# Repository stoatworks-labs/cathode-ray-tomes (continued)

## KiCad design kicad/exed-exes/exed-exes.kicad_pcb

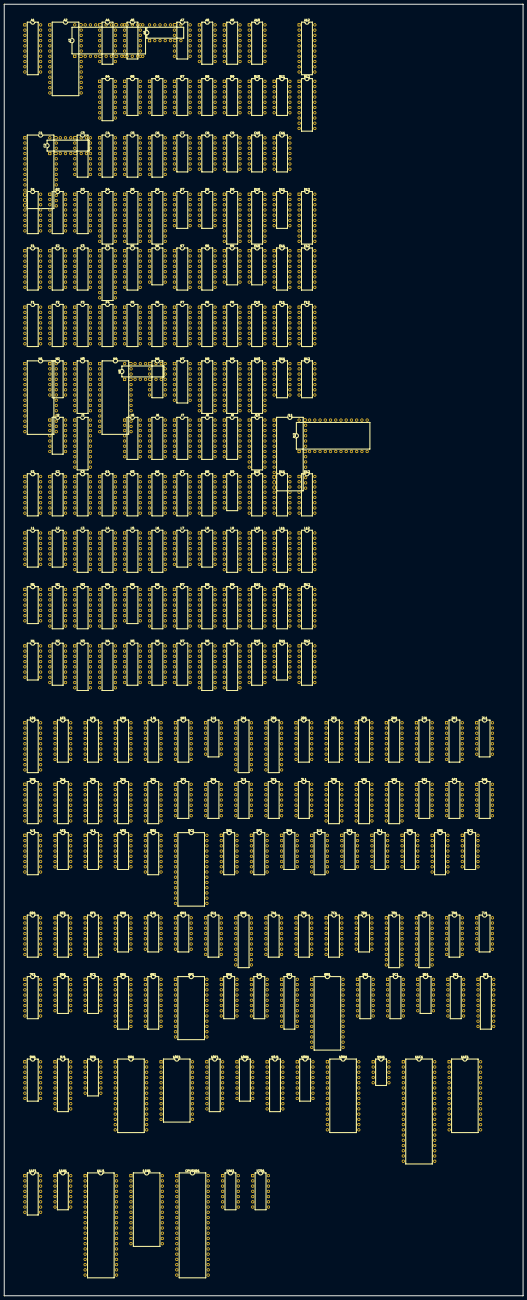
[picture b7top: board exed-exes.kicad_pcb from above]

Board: 2 copper layers, 251.8 x 626.8 mm, 235 parts (0 on the bottom side), 913 nets, no tracks yet.

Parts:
1D1, 7E1, 8D1, 8E1: 74LS273; DIP-20_W7.62mm
1E1, 2E1: 74LS153; DIP-16_W7.62mm
1F1, 1H1, 2F1, 2H1, 6E1, 7A1, 7C1, 7K1: 74LS174; DIP-16_W7.62mm
1J1, 1K1, 2J1, 2K1: 74LS161; DIP-16_W7.62mm
1L1, 5L1, 7D1: 74LS04; DIP-14_W7.62mm
2A1, 2B1, 7F1, 8K1, 9J1, 10F1, 10J1: 74LS245; DIP-20_W7.62mm
2D1, 3D1, 4D1, 6F1, 6L1: TBP24S10N; DIP-16_W7.62mm
2L1, 3J1, 3L1, 4H1, 4L1, 4M1, 6K1, 7J1: 74LS74; DIP-14_W7.62mm
2M1, 3A1, 4J1, 7B1, 9B1, 9E1, 10K1: 74LS138; DIP-16_W7.62mm
3B1: 74LS139; DIP-16_W7.62mm
3E1: TBP18S030; DIP-16_W7.62mm
3F1, 3H1: 74LS20; DIP-14_W7.62mm
3K1: 74LS30; DIP-14_W7.62mm
3M1: 74LS112; DIP-16_W7.62mm
4B1, 5B1, 5J1, 6B1, 8J1, 9C1: 74LS367; DIP-16_W7.62mm
4E1, 6H1: 74LS32; DIP-14_W7.62mm
4F1, 4K1, 5M1, 9D1, 9K1: 74LS08; DIP-14_W7.62mm
5C1: 2764; DIP-28_W15.24mm
5E1, 6D1: 74LS194; DIP-16_W7.62mm
5F1, 7H1, 8H1, 9H1: 74LS157; DIP-16_W7.62mm
5H1, 6J1: 74LS00; DIP-14_W7.62mm
5K1: 74LS10; DIP-14_W7.62mm
6C1: 74LS86; DIP-14_W7.62mm
6M1, 9F1: 74LS374; DIP-20_W7.62mm
8B1, 8C1: 74HC74; DIP-14_W7.62mm
8F1, 10E1: MSM2128-20RS; DIP-24_W15.24mm
8M1: TC5565; DIP-28_W15.24mm
9M1, 10M1, 11E1, 11M1: 27128; DIP-28_W15.24mm
10H1, 11F1: SN76489AN; DIP-16_W7.62mm
11A1: HA1368-R; DIP-10_W7.62mm
11C1: AY-3-8910; DIP-40_W15.24mm
11H1: 74LS14; DIP-14_W7.62mm
11J1: Z80CPU; DIP-40_W15.24mm
A1: 74LS273; DIP-20_W7.62mm
A2, A3: 27128; DIP-28_W15.24mm
A4: 74LS194; DIP-16_W7.62mm
A5, A6: 74LS74; DIP-14_W7.62mm
A7: 74LS32; DIP-14_W7.62mm
A8, A9, A10: 74LS161; DIP-16_W7.62mm
A12: 74LS245; DIP-20_W7.62mm
B4: 74LS194; DIP-16_W7.62mm
B5, B9: 74LS10; DIP-14_W7.62mm
B6: 74LS04; DIP-14_W7.62mm
B7: 74LS08; DIP-14_W7.62mm
B8: 74LS00; DIP-14_W7.62mm
B10, B11: MN2114; DIP-14_W7.62mm
B12: 74LS245; DIP-20_W7.62mm
C1: 27128; DIP-28_W15.24mm
C2, C3: 74LS194; DIP-16_W7.62mm
C4: TBP24S10N; DIP-16_W7.62mm
C5, C6: 74LS174; DIP-16_W7.62mm
C7, C10: 74LS32; DIP-14_W7.62mm
C8: 74LS08; DIP-14_W7.62mm
C9: 74LS04; DIP-14_W7.62mm
C11: 74LS74; DIP-14_W7.62mm
CPUSND1: Z80CPU; DIP-40_W15.24mm
D1, D2, D3: 74LS283; DIP-16_W7.62mm
D4, D5, D6: 74LS273; DIP-20_W7.62mm
D7, D8: MN2114; DIP-14_W7.62mm
D9, D10, D12: 74LS245; DIP-20_W7.62mm
D11: 74LS20; DIP-14_W7.62mm
E1, E2, E3, E11, E12: 74LS283; DIP-16_W7.62mm
E4: 74LS273; DIP-20_W7.62mm
E5: 74LS138; DIP-16_W7.62mm
E6: 74LS86; DIP-14_W7.62mm
E7, E8: 74LS157; DIP-16_W7.62mm
E9, E10: MN2114; DIP-14_W7.62mm
F1, F2: 74LS174; DIP-16_W7.62mm
F3, F4, F11, F12: 74LS283; DIP-16_W7.62mm
F5, F6: 74LS161; DIP-16_W7.62mm
F7, F8, F9, F10: 74LS157; DIP-16_W7.62mm
H1: 27128; DIP-28_W15.24mm
H2: 74LS86; DIP-14_W7.62mm
H3, H9, H10: 74LS273; DIP-20_W7.62mm
H4: 2764; DIP-28_W15.24mm
H5, H7: 74LS283; DIP-16_W7.62mm
H6: 74LS20; DIP-14_W7.62mm
H8: 74LS373; DIP-20_W7.62mm
H11, H12: 74LS04; DIP-14_W7.62mm
J2: 74LS86; DIP-14_W7.62mm
J3, J10: 74LS273; DIP-20_W7.62mm
J5, J7, J8: 74LS283; DIP-16_W7.62mm
J6: 74LS175; DIP-16_W7.62mm
J9: 74LS174; DIP-16_W7.62mm
J11, J12: 27128; DIP-28_W15.24mm
K1, K2, K10, K11, K12: 74LS194; DIP-16_W7.62mm
K3: 74LS157; DIP-16_W7.62mm
K4, K5: 74LS174; DIP-16_W7.62mm
K6: TBP24S10N; DIP-16_W7.62mm
K7: 74LS175; DIP-16_W7.62mm
K8: 74LS283; DIP-16_W7.62mm
K9: 74LS86; DIP-14_W7.62mm
L1: 74LS10; DIP-14_W7.62mm
L2, L7: 74LS04; DIP-14_W7.62mm
L3, L4, L9, L10: TBP24S10N; DIP-16_W7.62mm
L5, L6: 74LS139; DIP-16_W7.62mm
L8: 74LS32; DIP-14_W7.62mm
L11: 74LS157; DIP-16_W7.62mm
L12: 74LS194; DIP-16_W7.62mm
M1: 74LS74; DIP-14_W7.62mm
M2, M11: 74LS174; DIP-16_W7.62mm
M3, M4, M9, M10: 74LS257; DIP-16_W7.62mm
M5: 74LS00; DIP-14_W7.62mm
M6, M7, M8: 74LS163; DIP-16_W7.62mm
M12: 74LS157; DIP-16_W7.62mm
N1: 74LS74; DIP-14_W7.62mm
N2, N10: 74LS174; DIP-16_W7.62mm
N3, N4, N8, N9: HM6148; DIP-18_W7.62mm
N5, N6, N7: 74LS163; DIP-16_W7.62mm
N11: 74LS20; DIP-14_W7.62mm
N12: 74LS157; DIP-16_W7.62mm
U4K1: 74LS08; DIP-14_W7.62mm
U7D1: 74LS04; DIP-14_W7.62mm

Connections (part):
/main/ram_rom/ROM~CE1: 9K1.8, 9M1.20
/main/ram_rom/ROM~CE2: 9K1.6, 10M1.20
/main/ram_rom/ROM~CE3: 9K1.3, 11M1.20
/main/ram_rom/~CS01: 9K1.1, 10K1.15
/main/ram_rom/~CS23: 9K1.2, 10K1.14
/main/ram_rom/~CS45: 9K1.5, 10K1.13
/main/ram_rom/~CS67: 9K1.4, 10K1.12
/main/ram_rom/~CS89: 9K1.10, 10K1.11
/main/ram_rom/~CSAB: 9K1.9, 10K1.10
/main/ram_rom/~CSEF: 9K1.12, 10K1.7
/main/~WAIT: 6J1.8, 11J1.24
/sound/SA0: 9E1.1, 10E1.8, 11E1.10, CPUSND1.30
/sound/SA1: 9E1.2, 10E1.7, 11E1.9, CPUSND1.31
/sound/SA2: 9E1.3, 10E1.6, 11E1.8, CPUSND1.32
/sound/SA3: 10E1.5, 11E1.7, CPUSND1.33
/sound/SA4: 10E1.4, 11E1.6, CPUSND1.34
/sound/SA5: 10E1.3, 11E1.5, CPUSND1.35
/sound/SA6: 10E1.2, 11E1.4, CPUSND1.36
/sound/SA7: 10E1.1, 11E1.3, CPUSND1.37
/sound/SA8: 10E1.23, 11E1.25, CPUSND1.38
/sound/SA9: 10E1.22, 11E1.24, CPUSND1.39
/sound/SA10: 10E1.19, 11E1.21, CPUSND1.40
/sound/SA11: 11E1.23, CPUSND1.1
/sound/SA12: 11E1.2, CPUSND1.2
/sound/SA13: 9B1.1, 11E1.26, CPUSND1.3
/sound/SA14: 9B1.2, CPUSND1.4
/sound/SA15: 9B1.3, CPUSND1.5
/sound/snd_c_latch/SDB0: 10F1.11, 10H1.3, 11F1.3
/sound/snd_c_latch/SDB1: 10F1.12, 10H1.2, 11F1.2
/sound/snd_c_latch/SDB2: 10F1.13, 10H1.1, 11F1.1
/sound/snd_c_latch/SDB3: 10F1.14, 10H1.15, 11F1.15
/sound/snd_c_latch/SDB4: 10F1.15, 10H1.13, 11F1.13
/sound/snd_c_latch/SDB5: 10F1.16, 10H1.12, 11F1.12
/sound/snd_c_latch/SDB6: 10F1.17, 10H1.11, 11F1.11
/sound/snd_c_latch/SDB7: 10F1.18, 10H1.10, 11F1.10
/sound/snd_c_latch/SG_CLK: 8B1.3, 8B1.11, 8C1.11, 9C1.12, 9C1.13, 10H1.14, 11F1.14
/sound/snd_c_latch/VCC: 7B1.6, 8B1.1, 8B1.4, 8B1.10, 8B1.13, 8C1.10, 8C1.13, C11.1, E5.6
/sound/snd_c_latch/VSS: 9C1.1, 9C1.15, 10F1.1, C11.2
/sound/~SIORQ: 8C1.4, CPUSND1.20
/sound/~SMREQ: 9B1.4, CPUSND1.19
/sound/~SRAMCS: 9B1.13, 10E1.18
/sound/~SRFSH: 9B1.6, CPUSND1.28
/sound/~SROMCE: 9D1.11, 11E1.20
/video/char/0: 8D1.8, 8E1.2
/video/char/1: 8D1.7, 8E1.5
/video/char/2: 8D1.4, 8E1.6
/video/char/3: 8D1.3, 8E1.9
/video/char/4: 8D1.18, 8E1.12
/video/char/5: 8D1.17, 8E1.15
/video/char/6: 8D1.14, 8E1.16
/video/char/7: 8D1.13, 8E1.19
/video/char/AC0: 5C1.6, 8D1.9
/video/char/AC1: 5C1.5, 8D1.6
/video/char/AC2: 5C1.4, 8D1.5
/video/char/AC3: 5C1.3, 8D1.2
/video/char/AC4: 5C1.25, 8D1.19
/video/char/AC5: 5C1.24, 8D1.16
/video/char/AC6: 5C1.21, 8D1.15
/video/char/AC7: 5C1.23, 8D1.12
/video/char/AC8: 5C1.2, 7E1.19
/video/char/CC0: 6E1.15, 6F1.7
/video/char/CC1: 6E1.2, 6F1.4
/video/char/CC2: 6E1.5, 6F1.3
/video/char/CC3: 6E1.7, 6F1.2
/video/char/CC4: 6E1.10, 6F1.1
/video/char/CC5: 5F1.1, 6E1.12, 6F1.15
/video/char/CHAROM_A0: 6C1.9, 7C1.5
/video/char/CHAROM_A1: 6C1.13, 7C1.15
/video/char/CHAROM_A2: 6C1.4, 7C1.12
/video/char/CR_Q0: 5E1.15, 5F1.2
/video/char/CR_QQ0: 5F1.5, 6D1.15
/video/char/CR_QQ3: 5F1.6, 6D1.12
/video/char/DD0: 6E1.14, 7E1.2
/video/char/DD1: 6E1.3, 7E1.5
/video/char/DD2: 6E1.4, 7E1.6
/video/char/DD3: 6E1.6, 7E1.9
/video/char/DD4: 6E1.11, 7E1.12
/video/char/DD5: 6E1.13, 7D1.13, 7E1.15
/video/char/S0: 5E1.9, 5F1.9, 6D1.9
/video/char/S1: 5E1.10, 5F1.12, 6D1.10
/video/char/VFLIP: 6C1.5, 6C1.10, 6C1.12, 7E1.16
/video/colmix/CEX0: 1D1.17, 4E1.6
/video/colmix/CEX1: 1D1.8, 4E1.8
/video/colmix/CMUX0: 1D1.14, 2E1.7
/video/colmix/CMUX1: 1D1.7, 2E1.9
/video/colmix/CMUX2: 1D1.13, 1E1.9
/video/colmix/CMUX3: 1D1.4, 1E1.7
/video/colmix/COLA0: 1D1.15, 2D1.5, 3D1.5, 4D1.5
/video/colmix/COLA1: 1D1.6, 2D1.6, 3D1.6, 4D1.6
/video/colmix/COLA2: 1D1.12, 2D1.7, 3D1.7, 4D1.7
/video/colmix/COLA3: 1D1.5, 2D1.4, 3D1.4, 4D1.4
/video/colmix/COLA4: 1D1.16, 2D1.3, 3D1.3, 4D1.3
/video/colmix/COLA5: 1D1.9, 2D1.2, 3D1.2, 4D1.2
/video/colmix/COLA6: 1D1.19, 2D1.1, 3D1.1, 4D1.1
/video/colmix/COLA7: 1D1.2, 2D1.15, 3D1.15, 4D1.15
/video/colmix/CSEL0: 1D1.18, 1E1.14, 2E1.14, 3E1.1
/video/colmix/CSEL1: 1D1.3, 1E1.2, 2E1.2, 3E1.2
/video/colmix/CSEL2: 3E1.3, 4F1.5, 4F1.10
/video/colmix/CSEL3: 3E1.4, 4F1.2, 4F1.13
/video/colmix/OBJC0: 1F1.7, 2E1.4, 3F1.5
/video/colmix/OBJC1: 1F1.10, 2E1.12, 3F1.1
/video/colmix/OBJC2: 1E1.12, 1F1.12, 3F1.4
/video/colmix/OBJC3: 1E1.4, 1F1.5, 3F1.2
/video/colmix/OBJC4: 1F1.15, 4F1.1
/video/colmix/OBJC5: 1F1.2, 4F1.12
/video/colmix/S1C0: 2E1.5, 2F1.2, 3F1.13
/video/colmix/S1C1: 2E1.11, 2F1.7, 3F1.9
/video/colmix/S1C2: 1E1.11, 2F1.12, 3F1.10
/video/colmix/S1C3: 1E1.5, 2F1.15, 3F1.12
/video/colmix/S2C0: 1H1.10, 2E1.6
/video/colmix/S2C1: 1H1.12, 2E1.10
/video/colmix/S2C2: 1E1.10, 1H1.2
/video/colmix/S2C3: 1E1.6, 1H1.5
/video/colmix/S2C4: 1H1.7, 4F1.4
/video/colmix/S2C5: 1H1.15, 4F1.9
/video/h_scroll/SCR1X0: D3.5, D4.2
/video/h_scroll/SCR1X1: D3.3, D4.19
/video/h_scroll/SCR1X2: D3.14, D4.5
/video/h_scroll/SCR1X3: D3.12, D4.16
/video/h_scroll/SCR1X4: D2.5, D4.6
/video/h_scroll/SCR1X5: D2.3, D4.15
/video/h_scroll/SCR1X6: D2.14, D4.9
/video/h_scroll/SCR1X7: D2.12, D4.12
/video/h_scroll/SCR1X8: D1.5, F2.2
/video/h_scroll/SCR1X9: D1.3, F2.5
/video/h_scroll/SCR1X10: D1.14, F2.15
/video/h_scroll/SCR2X0: D6.2, F4.5
/video/h_scroll/SCR2X1: D6.19, F4.3
/video/h_scroll/SCR2X2: D6.5, F4.14
/video/h_scroll/SCR2X3: D6.16, F4.12
/video/h_scroll/SCR2X4: D6.6, F3.5
/video/h_scroll/SCR2X5: D6.15, F3.3
/video/h_scroll/SCR2X6: D6.9, F3.14
/video/h_scroll/SCR2X7: D6.12, F3.12
/video/h_scroll/SCR2X8: D5.2, H5.5
/video/h_scroll/SCR2X9: D5.5, H5.3
/video/h_scroll/SCR2X10: D5.6, H5.14
/video/h_scroll/SCR2X11: D5.9, H5.12
/video/h_scroll/SCR2X12: D5.12, J5.5
/video/h_scroll/SCR2X13: D5.15, J5.3
/video/h_scroll/SCR2X14: D5.16, J5.14
/video/h_scroll/SCR2X15: D5.19, J5.12
/video/h_scroll/XHMSB: B7.6, D1.2, D1.11, D1.15, H5.2, H5.11, H5.15, J5.2, J5.6, J5.11, J5.15
/video/h_scroll/YH7: D2.11, E6.8, F3.11
/video/h_scroll/~XH8: B7.2, B7.4, D1.6, H5.6, L2.6
/video/obj_counters/C0: N3.7, N4.7, N6.12
/video/obj_counters/C1: N3.6, N4.6, N6.13
/video/obj_counters/C2: N3.5, N4.5, N6.14
/video/obj_counters/C3: N3.4, N4.4, N6.11
/video/obj_counters/C4: M6.14, N3.3, N4.3
/video/obj_counters/C5: M6.13, N3.2, N4.2
/video/obj_counters/C6: M6.12, N3.1, N4.1
/video/obj_counters/C7: M6.11, N3.17, N4.17
/video/obj_counters/C_CLK: L7.12, M6.2, M7.2, M8.2, N5.2, N6.2, N7.2
/video/obj_counters/LMA0: M11.14, N8.14
/video/obj_counters/LMA1: M11.11, N8.13
/video/obj_counters/LMA2: M11.13, N8.12
/video/obj_counters/LMA3: M11.3, N8.11
/video/obj_counters/LMA4: N9.14, N10.14
/video/obj_counters/LMA5: N9.13, N10.11
/video/obj_counters/LMA6: N9.12, N10.13
/video/obj_counters/LMA7: N9.11, N10.3
/video/obj_counters/LMA_~CSB: N3.8, N4.8, N5.14
/video/obj_lut/C0: J7.7, K8.9
/video/obj_lut/OLSUM1: J8.6, K8.4
/video/obj_lut/OLSUM2: J8.2, K8.1
/video/obj_lut/OLSUM3: J8.15, K8.13
/video/obj_lut/OLSUM4: J8.11, K8.10
/video/obj_lut/OLSUM5: H7.6, J7.4
/video/obj_lut/OLSUM6: H7.2, J7.1
/video/obj_lut/OLSUM7: H7.15, J7.13
/video/obj_lut/OLSUM8: H7.11, J7.10
/video/obj_lut/OLUTA0: L9.5, L10.5, L11.12
/video/obj_lut/OLUTA1: L9.6, L10.6, L11.9
/video/obj_lut/OLUTA2: L9.7, L10.7, L11.7
/video/obj_lut/OLUTA3: L9.4, L10.4, L11.4
/video/obj_lut/OLUTA4: J9.7, L9.3, L10.3
/video/obj_lut/OLUTA5: J9.10, L9.2, L10.2
/video/obj_lut/OLUTA6: J9.12, L9.1, L10.1
/video/obj_lut/OLUTA7: J9.15, L9.15, L10.15
/video/obj_lut/V0_A0: K5.6, L2.8, L6.14
/video/obj_lut/rom_olut/OTMX_Q0: H10.2, J10.8
/video/obj_lut/rom_olut/OTMX_Q1: H10.5, J10.7
/video/obj_lut/rom_olut/OTMX_Q2: H10.6, J10.4
/video/obj_lut/rom_olut/OTMX_Q3: H10.9, J10.3
/video/obj_lut/rom_olut/OTMX_Q4: H10.12, J10.18
/video/obj_lut/rom_olut/OTMX_Q5: H10.15, J10.17
/video/obj_lut/rom_olut/OTMX_Q6: H10.16, J10.14
/video/obj_lut/rom_olut/OTMX_Q7: H10.19, J10.13
/video/obj_lut/~OLSUM: H6.6, K5.3
/video/obj_ram/CHA0: 8F1.8, 8H1.4
/video/obj_ram/CHA1: 8F1.7, 8H1.7
/video/obj_ram/CHA2: 8F1.6, 8H1.12
/video/obj_ram/CHA3: 8F1.5, 8H1.9
/video/obj_ram/CHA4: 8F1.4, 9H1.12
/video/obj_ram/CHA5: 8F1.3, 9H1.7
/video/obj_ram/CHA6: 8F1.2, 9H1.9
/video/obj_ram/CHA7: 8F1.1, 9H1.4
/video/obj_ram/CHA8: 7H1.12, 8F1.23
/video/obj_ram/CHA9: 7H1.7, 8F1.22
/video/obj_ram/CHA10: 7H1.4, 8F1.19
/video/obj_ram/OR_~OE: 7H1.9, 8F1.20
/video/object_table/OT0: B10.14, D9.2, D10.2, D12.18, E12.5
/video/object_table/OT1: B10.13, D9.3, D10.3, D12.17, E12.3
/video/object_table/OT2: B10.12, D9.4, D10.4, D12.16, E12.14
/video/object_table/OT3: B10.11, D9.5, D10.5, D12.15, E12.12
/video/object_table/OT4: B11.14, D9.6, D10.6, D12.14, E11.5
/video/object_table/OT5: B11.13, D9.7, D10.7, D12.13, E11.3
/video/object_table/OT6: B11.12, D9.8, D10.8, D12.12, E11.14
/video/object_table/OT7: B11.11, D9.9, D10.9, D12.11, E11.12
/video/object_table/OT_~WE: B10.10, B11.10, C10.3
/video/object_table/SV0: E11.15, F11.1
/video/object_table/SV1: E11.11, F11.4
/video/object_table/SV2: E11.6, F11.10
/video/object_table/SV3: E11.2, F11.13
/video/object_table/SV4: E12.2, F12.1
/video/object_table/SV5: E12.6, F12.4
/video/object_table/SV6: E12.11, F12.10
/video/object_table/SV7: E12.15, F12.13
/video/object_table/mux_ot/OAB0: E8.12, E9.5, E10.5
/video/object_table/mux_ot/OAB1: E8.7, E9.6, E10.6
/video/object_table/mux_ot/OAB2: E8.9, E9.7, E10.7
/video/object_table/mux_ot/OAB3: E8.4, E9.4, E10.4
/video/object_table/mux_ot/OAB4: E7.4, E9.3, E10.3
/video/object_table/mux_ot/OAB5: E7.12, E9.2, E10.2
/video/object_table/mux_ot/OAB6: E7.7, E9.1, E10.1
/video/object_table/mux_ot/OABC2: E8.11, F6.14, F8.14
/video/object_table/mux_ot/OABC3: E8.2, F6.13, F8.5
/video/object_table/mux_ot/OABC4: E7.2, F6.12, F7.5
/video/object_table/mux_ot/OABC5: E7.14, F6.11, F7.11
/video/object_table/mux_ot/OABC6: E7.5, F5.14, F7.2
/video/object_table/mux_ot/OBA0: D7.5, D8.5, F8.9
/video/object_table/mux_ot/OBA1: D7.6, D8.6, F8.4
/video/object_table/mux_ot/OBA2: D7.7, D8.7, F8.12
/video/object_table/mux_ot/OBA3: D7.4, D8.4, F8.7
/video/object_table/mux_ot/OBA4: D7.3, D8.3, F7.7
/video/object_table/mux_ot/OBA5: D7.2, D8.2, F7.9
/video/object_table/mux_ot/OBA6: D7.1, D8.1, F7.4
/video/object_table/mux_ot/OT_~WEA: D7.10, D8.10, F7.12
/video/object_table/mux_ot/OT_~WEB: E7.9, E9.10, E10.10
/video/object_table/mux_ot/OT~PEL: B7.8, F5.9, F6.9
/video/object_table/mux_ot/TC: F5.7, F5.10, F6.15
/video/object_table/mux_ot/~OTWEA: D11.8, E7.11, F7.14
/video/object_table/~C4IN: F11.7, F12.9
/video/object_table/~C4IN_A: E11.7, E12.9
/video/scroll1/PAL1A0: B4.15, C4.5
/video/scroll1/PAL1A1: A4.15, C4.6
/video/scroll1/PAL1A2: C2.15, C4.7
/video/scroll1/PAL1A3: C3.15, C4.4
/video/scroll1/PAL1A5: C4.2, C5.15
/video/scroll1/PAL1A6: C4.1, C5.12
/video/scroll1/PAL1A7: C4.15, C5.2
/video/scroll1/SCR1ON: B5.9, C6.10
/video/scroll2/HFLIP2: H2.2, H3.5, K4.11, L2.1
/video/scroll2/MAP2D0: H3.18, H4.11, K4.3
/video/scroll2/MAP2D1: H3.17, H4.12, K4.4
/video/scroll2/MAP2D2: H3.14, H4.13, K4.6
/video/scroll2/MAP2D3: H3.13, H4.15
/video/scroll2/MAP2D4: H3.8, H4.16
/video/scroll2/MAP2D5: H3.7, H4.17
/video/scroll2/MAP2D6: H3.4, H4.18
/video/scroll2/MAP2D7: H3.3, H4.19
/video/scroll2/SCR2A0: H1.10, H2.8, H2.12
/video/scroll2/SCR2A1: H1.9, H2.6
/video/scroll2/SCR2A2: H1.8, J2.11
/video/scroll2/SCR2A3: H1.7, J2.3
/video/scroll2/SCR2A4: H1.6, J2.6
/video/scroll2/SCR2A5: H1.5, J2.8
/video/scroll2/SCR2A6: H1.4, H2.11
/video/scroll2/SCR2A7: H1.3, H2.3
/video/scroll2/SCR2A8: H1.25, H3.19
/video/scroll2/SCR2A9: H1.24, H3.16
/video/scroll2/SCR2A10: H1.21, H3.15
/video/scroll2/SCR2A11: H1.23, H3.12
/video/scroll2/SCR2A12: H1.2, H3.9
/video/scroll2/SCR2A13: H1.26, H3.6
/video/scroll2/SCR2S0: K1.9, K2.9, K3.7
/video/scroll2/SCR2S1: K1.10, K2.10, K3.4
/video/scroll2/VFLIP2: H2.5, H3.2, J2.2, J2.5, J2.10, J2.13
/video/scroll2/~HFLIP2: H2.10, L2.2
/video/v_scroll/SCR1P0: E3.5, E4.9
/video/v_scroll/SCR1P1: E3.3, E4.12
/video/v_scroll/SCR1P2: E3.14, E4.6
/video/v_scroll/SCR1P3: E3.12, E4.15
/video/v_scroll/SCR1P4: E2.5, E4.5
/video/v_scroll/SCR1P5: E2.3, E4.16
/video/v_scroll/SCR1P6: E2.14, E4.2
/video/v_scroll/SCR1P7: E2.12, E4.19
/video/v_scroll/SCR1P8: E1.5, F1.2
/video/v_scroll/SCR1P9: E1.3, F1.5
/video/v_scroll/SCR1P10: E1.14, F1.15
A0: 8M1.10, 9M1.10, 10J1.3, 10M1.10, 11J1.30, 11M1.10
A0_~RD: 3A1.15, 6B1.1, 6B1.15
A1: 8M1.9, 9M1.9, 10J1.2, 10M1.9, 11J1.31, 11M1.9
A1_~RD: 3A1.14, 4B1.1, 4B1.15
A2: 8M1.8, 9M1.8, 10J1.9, 10M1.8, 11J1.32, 11M1.8
A2_~RD: 3A1.13, 5B1.1, 5B1.15
A3: 8M1.7, 9M1.7, 10J1.8, 10M1.7, 11J1.33, 11M1.7
A4: 8M1.6, 9M1.6, 10J1.7, 10M1.6, 11J1.34, 11M1.6
A5: 8M1.5, 9M1.5, 10J1.6, 10M1.5, 11J1.35, 11M1.5
A6: 8M1.4, 9M1.4, 10J1.5, 10M1.4, 11J1.36, 11M1.4
A7: 8M1.3, 9M1.3, 10J1.4, 10M1.3, 11J1.37, 11M1.3
A8: 8M1.25, 9J1.6, 9M1.25, 10M1.25, 11J1.38, 11M1.25
A9: 8M1.24, 9J1.5, 9M1.24, 10M1.24, 11J1.39, 11M1.24
A10: 8M1.21, 9J1.4, 9M1.21, 10M1.21, 11J1.40, 11M1.21
A11: 8M1.23, 9J1.3, 9M1.23, 10M1.23, 11J1.1, 11M1.23
A12: 8M1.2, 9J1.2, 9M1.2, 10M1.2, 11J1.2, 11M1.2
A13: 9M1.26, 10K1.1, 10M1.26, 11J1.3, 11M1.26
A14: 10K1.2, 11J1.4
A15: 10K1.3, 11J1.5
AB0: 3A1.1, 7B1.1, 8H1.3, 10J1.17, A12.2, E5.1
AB1: 3A1.2, 7B1.2, 8H1.6, 10J1.18, A12.3, E5.2
AB2: 3A1.3, 7B1.3, 8H1.13, 10J1.11, A12.4, E5.3
AB3: 8H1.10, 10J1.12, A12.5
AB4: 9H1.13, 10J1.13, A12.6
AB5: 9H1.6, 10J1.14, A12.7
AB6: 7B1.4, 9H1.10, 10J1.15, A12.8
AB7: 9H1.3, 10J1.16, A12.9
AB8: 7H1.10, 9J1.14, B9.3, B12.2, C11.12
AB9: 7H1.6, 9J1.15, B12.3
AB10: 7H1.3, 9J1.16, B12.4
AB11: 3B1.2, 9J1.17, B12.5
AB12: 3B1.3, 9J1.18, B12.7
BANK_WAIT: 3B1.10, 6J1.9
BLNB_~OE: L5.11, M9.15, M10.15
BOT11CN2: 4L1.5, 5F1.11, 5F1.13, 5M1.12
BSCR2_~OE: L5.12, M3.15, M4.15
BV0_~PE: L6.11, M7.9, M8.9, N7.9
BXH0_~PE: L6.12, M6.9, N5.9, N6.9
BXH_O2_LE: H8.11, L7.8
CHAR0: 2E1.3, 2H1.2, 3H1.10
CHAR1: 2E1.13, 2H1.12, 3H1.13
CHAR2: 1E1.13, 2H1.15, 3H1.9
CHAR3: 1E1.3, 2H1.5, 3H1.12
CHARCS: 6J1.10, 6J1.11, 7J1.1
CHB_~CE: 7F1.19, 7J1.6
CHD0: 7E1.3, 7F1.18, 8E1.3, 8F1.9
CHD1: 7E1.4, 7F1.16, 8E1.4, 8F1.10
CHD2: 7E1.7, 7F1.17, 8E1.7, 8F1.11
CHD3: 7E1.8, 7F1.15, 8E1.8, 8F1.13
CHD4: 7E1.13, 7F1.14, 8E1.13, 8F1.14
CHD5: 7E1.14, 7F1.12, 8E1.14, 8F1.15
CHD6: 7E1.17, 7F1.11, 8E1.17, 8F1.16
CHD7: 7E1.18, 7F1.13, 8E1.18, 8F1.17
CHON: 7A1.10, 7D1.3
CK6: 3J1.5, 3M1.13, 4L1.3, 4M1.3
CLK6: 4M1.2, 5J1.3, 5K1.12, 5L1.11, U7D1.11
COL_CLK: 4H1.5, 4H1.12
CPU_CLK: 8J1.3, 11J1.6
CPU_~RST: 11H1.8, 11J1.26
CR_CLK: 4L1.9, 7C1.9
D0: 6M1.16, 8K1.2, 8M1.11, 9M1.11, 10M1.11, 11J1.14, 11M1.11
D1: 6M1.15, 8K1.3, 8M1.12, 9M1.12, 10M1.12, 11J1.15, 11M1.12
D2: 6M1.19, 8K1.4, 8M1.13, 9M1.13, 10M1.13, 11J1.12, 11M1.13
D3: 6M1.9, 8K1.5, 8M1.15, 9M1.15, 10M1.15, 11J1.8, 11M1.15
D4: 6M1.6, 8K1.6, 8M1.16, 9M1.16, 10M1.16, 11J1.7, 11M1.16
D5: 6M1.5, 8K1.7, 8M1.17, 9M1.17, 10M1.17, 11J1.9, 11M1.17
D6: 6M1.2, 8K1.8, 8M1.18, 9M1.18, 10M1.18, 11J1.10, 11M1.18
D7: 6M1.12, 8K1.9, 8M1.19, 9M1.19, 10M1.19, 11J1.13, 11M1.19
DB0: 2A1.9, 2B1.9, 6B1.11, 7A1.3, 7F1.2, 8K1.18, 9F1.8, C5.14, D4.3, D5.3, D6.3, D12.2, E4.8, F1.3, F2.3
DB1: 2A1.8, 2B1.8, 6B1.5, 7A1.4, 7F1.4, 8K1.17, 9F1.13, C5.13, D4.18, D5.18, D6.18, D12.3, E4.13, F1.4, F2.4
DB2: 2A1.7, 2B1.7, 4B1.9, 5B1.9, 6B1.9, 7F1.3, 8K1.16, 9F1.14, C5.3, D4.4, D5.4, D6.4, D12.4, E4.7, F1.14, F2.14
DB3: 2A1.6, 2B1.6, 4B1.7, 5B1.7, 6B1.7, 7F1.5, 8K1.15, 9F1.7, D4.17, D5.17, D6.17, D12.5, E4.14
DB4: 2A1.5, 2B1.5, 4B1.11, 5B1.11, 7A1.6, 7F1.6, 8K1.14, 9F1.4, C5.6, C6.6, D4.7, D5.7, D6.7, D12.6, E4.4
DB5: 2A1.4, 2B1.4, 4B1.5, 5B1.5, 7F1.8, 8K1.13, 9F1.17, C5.11, C6.11, D4.14, D5.14, D6.14, D12.7, E4.17
DB6: 2A1.3, 2B1.3, 4B1.13, 5B1.13, 6B1.13, 7F1.9, 8K1.12, 9F1.18, C5.4, C6.4, D4.8, D5.8, D6.8, D12.8, E4.3
DB7: 2A1.2, 2B1.2, 4B1.3, 5B1.3, 6B1.3, 7A1.11, 7F1.7, 8K1.11, 9F1.3, D4.13, D5.13, D6.13, D12.9, E4.18
DIPACS: 2A1.19, 3A1.12
DIPBCS: 2B1.19, 3A1.11
DIR: 4K1.2, 9J1.1, 9K1.13, 10J1.1
DRLUT_CLK: K10.11, K11.11, K12.11, L8.11, L12.11
DR_LUT_H0: K12.12, L11.3
DR_LUT_H1: L11.6, L12.12
DR_LUT_H2: K11.12, L11.10
DR_LUT_H3: K10.12, L11.13
DR_LUT_L0: K12.15, L11.2
DR_LUT_L1: L11.5, L12.15
DR_LUT_L2: K11.15, L11.11
DR_LUT_L3: K10.15, L11.14
GFXONCS: C6.9, E5.7
H0: 5J1.9, 8J1.2, 9C1.14
H1: 3B1.14, 5J1.7, 7H1.2
H2: 3B1.13, 5J1.11, 6C1.1, 7H1.1, 7J1.3, 8H1.1, 9H1.1
HS_X3: F4.10, H2.13
HS_X4: F3.4, N1.2
INT_V_CLK: 6M1.11, 7K1.9, 8J1.11
IO2CS: 3B1.5, 7B1.5
LMA'0: M2.15, M4.13, M9.13, M11.15, M12.13, M12.14, N11.1, N11.9
LMA'1: M2.10, M4.10, M9.10, M11.10, M12.10, M12.11, N11.4, N11.10
LMA'2: M2.12, M4.6, M9.6, M11.12, M12.5, M12.6, N11.5, N11.12
LMA'3: M2.2, M4.3, M9.3, M11.2, M12.2, M12.3, N11.2, N11.13
LMA'4: M3.13, M10.13, N2.15, N10.15, N12.13, N12.14
LMA'5: M3.10, M10.10, N2.10, N10.10, N12.10, N12.11
LMA'6: M3.6, M10.6, N2.12, N10.12, N12.5, N12.6
LMA'7: M3.3, M10.3, N2.2, N10.2, N12.2, N12.3
LMA_~CSA: M8.14, N8.8, N9.8
LMA_~WEA: M5.6, N8.10, N9.10
LMA_~WEB: M5.3, N3.10, N4.10
LMB0: M2.14, M4.12, N4.14
LMB1: M2.11, M4.9, N4.13
LMB2: M2.13, M4.7, N4.12
LMB3: M2.3, M4.4, N3.11
LMB4: M3.12, N2.14, N3.12
LMB5: M3.9, N2.11, N3.13
LMB6: M3.7, N2.13, N3.14
LMB7: M3.4, N2.3, N4.11
LNA_~MR: L5.6, M5.4, M7.1, M8.1, M11.1, N7.1, N10.1
LNB_~MR: L5.7, M2.1, M5.1, M6.1, N2.1, N5.1, N6.1
LN_CLK: K5.7, L5.14, M2.9, M5.2, M5.5, M11.9, N2.9, N10.9
LV0: E3.6, H2.4, J3.19
LV1: E3.2, J2.12, J3.16
LV2: E3.15, J2.1, J3.15
LV3: E3.11, J2.4, J3.12
LV4: E2.6, J2.9, J3.9
LV5: E2.2, H4.7, J3.6
LV6: E2.15, H4.6, J3.5
LV7: E2.11, H4.5, J3.2
LVBL: 3L1.9, 5H1.12
LV_CLK: J3.11, J9.9, K5.9
MAIN~RD: 3A1.5, 6J1.1, 7F1.1, 7H1.13, 9J1.13, 11H1.1, B12.6, B12.9
MAP1A0: C1.10, D2.4
MAP1A1: C1.9, D2.1
MAP1A2: C1.8, D2.13
MAP1A3: C1.7, D2.10
MAP1A4: C1.6, E2.4
MAP1A5: C1.5, E2.1
MAP1A6: C1.4, E2.13
MAP1A7: C1.3, E2.10
MAP1A8: C1.25, D1.4
MAP1A9: C1.24, D1.1
MAP1A10: C1.21, D1.13
MAP1A11: C1.23, E1.4
MAP1A12: C1.2, E1.1
MAP1A13: C1.26, E1.13
MAP2A0: F3.1, H4.10
MAP2A1: F3.13, H4.9
MAP2A2: F3.10, H4.8
MAP2A6: F4.13, H2.9, H4.4, L1.5, L2.13
MAP2A7: H4.3, H5.4
MAP2A8: H4.25, H5.1
MAP2A9: H4.24, H5.13
MAP2A10: H4.21, H5.10
MAP2A11: H4.23, J5.4
MAP2A12: H4.2, J5.1
MAP2SCR0: L1.6, L1.9, M1.2
MAP2SCR1: L1.10, L1.11, L1.12, M1.12
unnamed: 1D1.1, 4H1.8
unnamed: 1J1.7, 1J1.10, 2J1.15
unnamed: 1J1.9, 1L1.8, 2J1.9
unnamed: 1K1.7, 1K1.10, 2K1.15
unnamed: 1K1.15, 1L1.13
unnamed: 1K1.9, 1L1.12, 2K1.9
unnamed: 2H1.3, 6F1.12
unnamed: 2H1.4, 6F1.9
unnamed: 2H1.13, 6F1.11
unnamed: 2H1.14, 6F1.10
unnamed: 2L1.2, 2L1.6
unnamed: 2M1.4, 3L1.6, 3L1.12
unnamed: 2M1.12, 4K1.9
unnamed: 3A1.4, 3B1.4
unnamed: 3E1.10, 3F1.8
unnamed: 3E1.11, 3F1.6
unnamed: 3E1.13, 3H1.8
unnamed: 1L1.4, 3J1.3
unnamed: 3L1.1, 5K1.8
unnamed: 3K1.8, 3L1.4
unnamed: 3M1.11, 5M1.8
unnamed: 3M1.12, 5M1.6
unnamed: 4E1.4, 4F1.6
unnamed: 4E1.5, 4F1.3
unnamed: 4E1.9, 4F1.11
unnamed: 4E1.10, 4F1.8
unnamed: 4H1.2, 5H1.11
unnamed: 4J1.12, 4K1.12
unnamed: 4J1.11, 4K1.13
unnamed: 4K1.10, 4K1.11
unnamed: 4L1.2, 5M1.3
unnamed: 4L1.12, 5M1.11
unnamed: 4M1.5, 4M1.12
unnamed: 5C1.10, 6C1.3
unnamed: 5C1.9, 6C1.11
unnamed: 5C1.8, 6C1.6
unnamed: 5C1.7, 6C1.8
unnamed: 5C1.11, 6D1.6
unnamed: 5C1.12, 6D1.5
unnamed: 5C1.13, 6D1.4
unnamed: 5C1.15, 6D1.3
unnamed: 5C1.16, 5E1.6
unnamed: 5C1.17, 5E1.5
unnamed: 5C1.18, 5E1.4
unnamed: 5C1.19, 5E1.3
unnamed: 5F1.4, 6F1.5
unnamed: 5F1.7, 6F1.6
unnamed: 5K1.11, 5L1.12
unnamed: 5L1.2, 5M1.9
unnamed: 6C1.2, 7D1.12
unnamed: 6F1.13, 6F1.14, 7D1.4
unnamed: 6J1.3, 6J1.4
unnamed: 6K1.3, 7K1.10
unnamed: 6K1.12, 6L1.9
unnamed: 6K1.9, 7K1.11
unnamed: 6L1.12, 6M1.8
unnamed: 6L1.11, 6M1.7
unnamed: 6L1.10, 7K1.6
unnamed: 7B1.15, 9F1.11
unnamed: 7D1.9, U7D1.10
unnamed: 6J1.2, 7J1.5
unnamed: 7J1.8, 7J1.12
unnamed: 6J1.6, 7J1.10
unnamed: 4E1.2, 8B1.5, 8B1.12
unnamed: 4E1.1, 8B1.8
unnamed: 8C1.5, CPUSND1.16
unnamed: 8C1.8, 8C1.12
unnamed: 5H1.3, 8K1.1
unnamed: 4K1.3, 8K1.19
unnamed: 8M1.20, 9K1.11
unnamed: 9B1.15, 9D1.12
unnamed: 9B1.14, 9D1.13
unnamed: 9D1.3, 9D1.4
unnamed: 7D1.2, 11C1.29
unnamed: 5H1.6, 11C1.27
unnamed: 5H1.1, 11H1.2
unnamed: 11H1.3, 11H1.5, 11H1.9, 11H1.10
unnamed: A1.11, A5.6
unnamed: A1.3, C1.11
unnamed: A1.4, C1.12
unnamed: A1.7, C1.13
unnamed: A1.8, C1.15
unnamed: A1.13, C1.16
unnamed: A1.14, C1.17
unnamed: A1.17, C1.18
unnamed: A1.18, C1.19
unnamed: A2.11, C3.6
unnamed: A2.12, C3.5
unnamed: A2.13, C3.4
unnamed: A2.15, C3.3
unnamed: A2.16, C2.6
unnamed: A2.17, C2.5
unnamed: A2.18, C2.4
unnamed: A2.19, C2.3
unnamed: A3.11, A4.6
unnamed: A3.12, A4.5
unnamed: A3.13, A4.4
unnamed: A3.15, A4.3
unnamed: A3.16, B4.6
unnamed: A3.17, B4.5
unnamed: A3.18, B4.4
unnamed: A3.19, B4.3
unnamed: A5.9, A6.11
unnamed: A6.3, B6.4
unnamed: A6.2, K6.10
unnamed: A7.5, B6.6
unnamed: A7.8, C8.2
unnamed: A7.11, B6.1
unnamed: A7.12, C8.6, C8.9, C9.13
unnamed: A8.4, B9.8
unnamed: B6.2, B7.13
unnamed: B6.8, B7.1
unnamed: B7.3, E6.10
unnamed: B8.3, B8.4, C9.5, C10.4
unnamed: B8.5, B9.12
unnamed: B8.6, B8.12
unnamed: B9.5, C7.3
unnamed: B5.8, C4.13, C4.14
unnamed: C7.2, C9.12
unnamed: C7.6, C8.1
unnamed: C7.9, C8.8
unnamed: C8.5, C9.10
unnamed: C9.8, D11.12
unnamed: C8.13, C10.6
unnamed: C9.6, C10.9, C10.12
unnamed: 9D1.6, CPUSND1.24
unnamed: D1.7, D2.9
unnamed: D2.7, D3.9
unnamed: B5.1, B5.4, D3.4
unnamed: B5.2, B5.3, D3.1
unnamed: B5.13, B6.11, D3.13
unnamed: D3.10, E6.13
unnamed: E1.7, E2.9
unnamed: E2.7, E3.9
unnamed: E6.2, H12.8
unnamed: D11.4, E11.4
unnamed: D11.5, E11.1
unnamed: D11.2, E11.13
unnamed: D11.1, E11.10
unnamed: F3.7, F4.9
unnamed: F3.9, H5.7
unnamed: F4.4, L1.2, L1.3
unnamed: F4.1, L1.1, L1.4
unnamed: F11.6, H11.2
unnamed: F11.2, H11.4
unnamed: F11.15, H11.10
unnamed: F11.11, H11.12
unnamed: F12.6, H12.2
unnamed: F12.2, H12.4
unnamed: F12.15, H12.10
unnamed: F12.11, H12.12
unnamed: H1.11, K2.6
unnamed: H1.12, K2.5
unnamed: H1.13, K2.4
unnamed: H1.15, K2.3
unnamed: H1.16, K1.6
unnamed: H1.17, K1.5
unnamed: H1.18, K1.4
unnamed: H1.19, K1.3
unnamed: H5.9, J5.7
unnamed: H7.7, J8.9
unnamed: H6.2, H7.4
unnamed: H6.1, H7.1
unnamed: H6.4, H7.13
unnamed: H6.5, H7.10
unnamed: H11.6, L8.4
unnamed: H11.8, K9.2, K9.5, K9.10, K9.13
unnamed: H12.6, L7.13
unnamed: J8.4, K9.9
unnamed: J8.1, K9.12
unnamed: J8.13, K9.1
unnamed: J8.10, K9.4
unnamed: J11.11, K11.6
unnamed: J11.12, K11.5
unnamed: J11.13, K11.4
unnamed: J11.15, K11.3
unnamed: J11.16, K10.6
unnamed: J11.17, K10.5
unnamed: J11.18, K10.4
unnamed: J11.19, K10.3
unnamed: J12.11, K12.6
unnamed: J12.12, K12.5
unnamed: J12.13, K12.4
unnamed: J12.15, K12.3
unnamed: J12.16, L12.6
unnamed: J12.17, L12.5
unnamed: J12.18, L12.4
unnamed: J12.19, L12.3
unnamed: K1.15, K3.11
unnamed: K1.12, K3.10
unnamed: K2.15, K3.14
unnamed: K2.12, K3.13
unnamed: K3.3, K3.5, L1.8
unnamed: K3.1, K4.10
unnamed: K4.9, M1.6
unnamed: K5.2, L7.5
unnamed: L1.13, L2.12
unnamed: L2.9, L2.10
unnamed: L2.4, L3.13, L3.14, L4.13, L4.14
unnamed: L5.3, L7.4
unnamed: L6.6, L7.9
unnamed: L6.7, L7.11
unnamed: L6.13, M5.8
unnamed: L7.6, M5.13
unnamed: L7.10, M5.9
unnamed: L9.13, L9.14, L10.13, L10.14, M5.11
unnamed: M6.7, M6.10, N6.15
unnamed: M6.15, N5.7, N5.10
unnamed: M7.7, M7.10, N7.15
unnamed: M7.14, N8.3, N9.3
unnamed: M7.13, N8.2, N9.2
unnamed: M7.12, N8.1, N9.1
unnamed: M7.11, N8.17, N9.17
unnamed: M7.15, M8.7, M8.10
unnamed: H2.1, N1.5
unnamed: N7.14, N8.5, N9.5
unnamed: N7.13, N8.6, N9.6
unnamed: N7.12, N8.7, N9.7
unnamed: N7.11, N8.4, N9.4
OABC_CLK: A7.10, C9.1, C11.8
OBJ0: 1F1.6, M12.12
OBJ1: 1F1.11, M12.9
OBJ2: 1F1.13, M12.7
OBJ3: 1F1.4, M12.4
OBJ4: 1F1.14, N12.12
OBJ5: 1F1.3, N12.9
OBJ7: 2H1.11, N12.4
OBJON: C6.5, M5.12
OC0: A8.14, A12.18, B10.5, B11.5, E8.14, F8.11
OC1: A8.13, A12.17, B10.6, B11.6
OC2: A10.14, A12.13, B10.7, B11.7
OC3: A10.13, A12.12, B10.4, B11.4
OC4: A10.12, A12.11, B10.3, B11.3
OC5: A10.11, B10.2, B11.2, B12.18
OC6: A9.14, B9.1, B10.1, B11.1, B12.17
OC7: A9.13, B8.1, B12.16
OC8: A9.12, B8.2, B9.13, B12.15
OCOUN_CLK: H12.5, L5.13, L8.3, L8.12
OC_D3: B8.11, B9.4
OC_Q3: A8.11, C9.11, D11.10
OLUT0: L9.12, M4.14, M9.14
OLUT1: L9.11, M4.11, M9.11
OLUT2: L9.10, M4.5, M9.5
OLUT3: L9.9, M4.2, M9.2
OLUT4: L10.12, M3.14, M10.14
OLUT5: L10.11, M3.11, M10.11
OLUT6: L10.10, M3.5, M10.5
OLUT7: J9.2, M3.2, M10.2
OR_~WE: 7J1.9, 8F1.21
OTAB0: D10.18, E9.14, F9.14
OTAB1: D10.17, E9.13, F9.11
OTAB2: D10.16, E9.12, F9.5
OTAB3: D10.15, E9.11, F9.2
OTAB4: D10.14, E10.14, F10.14
OTAB5: D10.13, E10.13, F10.11
OTAB6: D10.12, E10.12, F10.5
OTAB7: D10.11, E10.11, F10.2
OTBA0: D7.14, D9.18, F9.13
OTBA1: D7.13, D9.17, F9.10
OTBA2: D7.12, D9.16, F9.6
OTBA3: D7.11, D9.15, F9.3
OTBA4: D8.14, D9.14, F10.13
OTBA5: D8.13, D9.13, F10.10
OTBA6: D8.12, D9.12, F10.6
OTBA7: D8.11, D9.11, F10.3
OTCQ1: B6.13, F5.13
OT_CEP_C: A10.7, A10.10, C7.8
OT_CLK: A6.5, A7.2, A7.4, C7.4, F9.15, F10.15
OT_MUX0: F10.12, H8.3, H9.3, H10.3, M6.3, M7.3
OT_MUX1: F10.9, H8.4, H9.4, H10.4, M6.4, M7.4
OT_MUX2: F10.7, H8.7, H9.7, H10.7, M6.5, M7.5
OT_MUX3: F10.4, H8.8, H9.8, H10.8, M6.6, M7.6
OT_MUX4: F9.4, H8.13, H9.13, H10.13, N6.6, N7.6
OT_MUX5: F9.7, H8.14, H9.14, H10.14, N6.5, N7.5
OT_MUX6: F9.9, H8.17, H9.17, H10.17, N6.4, N7.4
OT_MUX7: F9.12, H8.18, H9.18, H10.18, N6.3, N7.3
OT_MUX'0: H9.2, H12.9, J9.4
OT_MUX'1: H9.5, H11.9
OT_MUX'2: H9.6, J9.3
OT_MUX'3: H9.9, M8.3, N5.3
OT_MUX'4: H9.12, J9.14
OT_MUX'5: H9.15, J9.13
OT_MUX'6: H9.16, J9.11
OT_MUX'7: H9.19, J9.6
OT_OL'0: H7.5, H8.2
OT_OL'1: H7.3, H8.5
OT_OL'2: H7.12, H8.6
OT_OL'3: H7.14, H8.9
OT_OL'4: H8.12, J8.12
OT_OL'5: H8.15, J8.14
OT_OL'6: H8.16, J8.3
OT_OL'7: H8.19, J8.5
OT_RQB: C11.6, C11.10
OT_TC1: A7.13, A8.15, C7.10, C8.4, E8.5, F6.7, F6.10, F8.2
OT_~AB8: A8.5, A8.6, B9.6, B9.9
OT_~CEA: C10.11, D9.19
OT_~CEB: A12.19, B12.19, C9.2, C10.2, D10.19
OT_~CEC: C10.8, D12.19
OT_~PEA: A8.9, B7.11
OT_~PEB: A9.9, A10.9, B7.12, C8.3
PAL2A0: K3.9, L3.5, L4.5
PAL2A1: K3.12, L3.6, L4.6
PAL2A2: K4.2, L3.7, L4.7
PAL2A3: K4.5, L3.4, L4.4
PAL2A4: K4.7, L3.3, L4.3
PAL2A5: C5.7, L3.2, L4.2
PAL2A6: C5.10, L3.1, L4.1
PAL2A7: C5.5, L3.15, L4.15
PALBANKCS: C5.9, E5.9
PORB: 7A1.1, 9C1.10, 11H1.4
PRIOA2: 2H1.10, 3E1.12
PSG_CLK: 8C1.9, 11C1.22
ROLUTA0: E6.3, E6.4, J11.10, J12.10
ROLUTA1: J11.9, J12.9, K9.8
ROLUTA2: J11.8, J12.8, K9.11
ROLUTA3: J11.7, J12.7, K9.3
ROLUTA4: J11.6, J12.6, K9.6
ROLUTA5: E6.6, J11.5, J12.5
ROLUTA6: J10.12, J11.4, J12.4
ROLUTA7: J10.15, J11.3, J12.3
ROLUTA8: J10.16, J11.25, J12.25
ROLUTA9: J10.19, J11.24, J12.24
ROLUTA10: J10.9, J11.21, J12.21
ROLUTA11: J10.6, J11.23, J12.23
ROLUTA12: J10.5, J11.2, J12.2
ROLUTA13: J10.2, J11.26, J12.26
S2F: 1J1.15, 1L1.9, 1L1.11, 2L1.12
SCLK: 9C1.11, CPUSND1.6
SCR1A: 2F1.3, C4.12
SCR1A0: A2.10, A3.10, B5.5, B6.10, E6.12
SCR1A1: A2.9, A3.9, E3.4
SCR1A2: A2.8, A3.8, E3.1
SCR1A3: A2.7, A3.7, E3.13
SCR1A4: A2.6, A3.6, E3.10
SCR1A5: A2.5, A3.5, E6.11
SCR1A6: A1.2, A2.4, A3.4
SCR1A7: A1.5, A2.3, A3.3
SCR1A8: A1.6, A2.25, A3.25
SCR1A9: A1.9, A2.24, A3.24
SCR1A10: A1.12, A2.21, A3.21
SCR1A11: A1.15, A2.23, A3.23
SCR1A12: A1.16, A2.2, A3.2
SCR1A13: A1.19, A2.26, A3.26, A6.12
SCR1B: 2F1.6, C4.11
SCR1C: 2F1.13, C4.10
SCR1D: 2F1.14, C4.9
SCR1S0: A4.9, B4.9, B8.8, C2.9, C3.9
SCR1X0CS: D4.11, E5.15
SCR1X1CS: E5.14, F2.9
SCR1Y0CS: E4.11, E5.13
SCR1Y1CS: E5.12, F1.9
SCR2A: 1H1.11, L4.12
SCR2B: 1H1.13, L4.11
SCR2C: 1H1.3, L4.10
SCR2D: 1H1.4, L4.9
SCR2E: 1H1.6, L3.12
SCR2F: 1H1.14, L3.11
SCR2ON: C6.7, L2.3
SCR2X0CS: D6.11, E5.11
SCR2X1CS: D5.11, E5.10
SCR2_CLK: A4.11, A5.3, A5.11, B4.11, C2.11, C3.11, K1.11, K2.11, L8.1, M1.3, M1.11
SCR_CLK: A5.12, B5.12, B8.10
SD0: 9F1.9, 10E1.9, 10F1.9, 11C1.37, 11E1.11, CPUSND1.14
SD1: 9F1.12, 10E1.10, 10F1.8, 11C1.36, 11E1.12, CPUSND1.15
SD2: 9F1.15, 10E1.11, 10F1.7, 11C1.35, 11E1.13, CPUSND1.12
SD3: 9F1.6, 10E1.13, 10F1.6, 11C1.34, 11E1.15, CPUSND1.8
SD4: 9F1.5, 10E1.14, 10F1.5, 11C1.33, 11E1.16, CPUSND1.7
SD5: 9F1.16, 10E1.15, 10F1.4, 11C1.32, 11E1.17, CPUSND1.9
SD6: 9F1.19, 10E1.16, 10F1.3, 11C1.31, 11E1.18, CPUSND1.10
SD7: 9F1.2, 10E1.17, 10F1.2, 11C1.30, 11E1.19, CPUSND1.13
SG_RDY1: 9D1.1, 10H1.4
SG_RDY2: 9D1.2, 11F1.4
SICLK: 8C1.3, 9C1.3
SINT: 7K1.7, 9C1.2
SINT_CLK: 6K1.11, 8J1.13
SND_~RQB: C8.11, C11.4
SND_~WAIT: 4E1.3, 9D1.5, 10F1.19
SOLUTA: H11.5, J9.5, L8.9, L11.1
SRQB: 11H1.6, C8.12
S_OLUTA: L8.5, L8.10
S_OLUTA0: K10.9, K11.9, K12.9, L8.8, L12.9
S_OLUTA1: K10.10, K11.10, K12.10, L8.6, L12.10
S_OMUX: K5.5, L5.2, L5.15, M12.1, N12.1
TC_COT2: A9.7, A9.10, A10.15, B9.2
V0: 2K1.7, 2K1.10, 2L1.5, 6L1.5, 7C1.14, H11.3, J3.18, K6.5, K7.12, L2.11, L7.1
V1: 2K1.14, 6L1.6, 7C1.13, H11.1, J3.17, K6.6, K7.4
V2: 2K1.13, 6L1.7, 7C1.4, H11.13, J3.14, K6.7, K7.13
V3: 2K1.12, 2M1.1, 6L1.4, 9H1.5, H11.11, J3.13, K6.4, K7.5
V4: 2K1.11, 3K1.5, 5K1.10, 6L1.3, 9H1.11, H12.3, J3.8, J6.12, K6.3
V5: 1K1.14, 3K1.4, 6L1.2, 9H1.2, H12.1, J3.7, J6.4, K6.2
V6: 1K1.13, 3K1.3, 6L1.1, 7H1.14, H12.13, J3.4, J6.13, K6.1
V7: 1K1.12, 2M1.2, 3K1.11, 5L1.13, 7H1.5, H12.11, J3.3, J6.5, K6.15
V8: 1K1.11, 2M1.3, 3K1.6, 5K1.9
VC2CS: 3B1.7, E5.4, E5.5
VCC: 1J1.1, 1J1.5, 1K1.1, 1K1.3, 1K1.4, 1K1.5, 1L1.14, 2D1.16, 2H1.1, 2J1.1, 2K1.1, 2K1.3, 2K1.5, 2K1.6, 2L1.1, 2L1.4, 2L1.10, 2L1.13, 2M1.6, 3A1.6, 3D1.16, 3J1.1, 3J1.4, 3J1.10, 3J1.13, 3K1.1, 3K1.2, 3K1.12, 3L1.10, 3L1.13, 3M1.10, 3M1.14, 4D1.16, 4E1.14, 4H1.1, 4H1.4, 4H1.10, 4H1.13, 4H1.14, 4J1.6, 4L1.1, 4L1.4, 4L1.10, 4L1.13, 4M1.4, 4M1.10, 4M1.13, 5C1.1, 5C1.27, 5C1.28, 5E1.1, 5F1.10, 5F1.14, 5H1.14, 6D1.1, 6E1.1, 6F1.16, 6J1.5, 6J1.12, 6K1.1, 6K1.10, 6L1.15, 6L1.16, 6M1.3, 6M1.13, 6M1.14, 6M1.17, 6M1.18, 7C1.1, 7D1.14, 7E1.1, 7J1.2, 7J1.4, 7J1.13, 7K1.1, 8C1.1, 8D1.1, 8E1.1, 8F1.24, 8M1.26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
VCLK: 1K1.2, 2K1.2, 2L1.3, 2L1.9
VCTRL1CS: 7A1.9, 7B1.11
VS'_CLK: J6.9, K7.9
VSROM_Q0: K5.4, K6.12, L6.15
VSROM_Q1: K5.11, K6.11
VSROM_Q1': K5.10, L5.1, M12.15, N12.15
VSS: 1E1.1, 1E1.15, 1F1.1, 1H1.1, 1J1.3, 1J1.4, 1J1.6, 1K1.6, 1L1.7, 2A1.1, 2B1.1, 2D1.8, 2D1.13, 2D1.14, 2E1.1, 2E1.15, 2F1.1, 2J1.3, 2J1.4, 2J1.5, 2J1.6, 2K1.4, 2M1.5, 3B1.15, 3D1.8, 3D1.13, 3D1.14, 3E1.14, 3E1.15, 3L1.2, 3L1.3, 4D1.8, 4D1.13, 4D1.14, 4E1.7, 4H1.7, 4J1.5, 5C1.14, 5C1.20, 5C1.22, 5E1.2, 5E1.7, 5E1.12, 5F1.3, 5F1.15, 5H1.7, 5J1.1, 5J1.15, 6D1.2, 6D1.7, 6F1.8, 6K1.2, 6L1.8, 6L1.13, 6L1.14, 6M1.4, 7D1.7, 7H1.11, 7H1.15, 8C1.2, 8F1.12, 8F1.18, 8H1.15, 8J1.1, 8J1.15, 9B1.5, 9D1.7, 9H1.15, 9J1.19, 9M1.14, 9M1.22, 10E1.12, 10J1.19, 10K1.4, 10M1.14, 10M1.22, 11A1.8, 11C1.1, 11C1.24, 11E1.14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
VS_~FF0: K7.3, K8.2
VS_~FF1: K7.6, K8.11
VS_~FF2: K7.11, K8.6
VS_~FF3: K7.14, K8.15
VS_~FF4: J6.3, J7.2
VS_~FF5: J6.6, J7.11
VS_~FF6: J6.11, J7.6
VS_~FF7: J6.14, J7.15
VT_CLK6: 1D1.11, 1F1.9, 1H1.9, 2F1.9, 2H1.9, 5E1.11, 6D1.11, 7D1.5, 7D1.8
X6M: 1J1.2, 2J1.2, 2L1.11, 3J1.2, 3J1.6, 3J1.11, 4L1.11, 4M1.11, 5J1.2
XH0: 2J1.7, 2J1.10, 3J1.9, 5K1.2, 5M1.1, 7J1.11, 8J1.12, D3.6, F4.6, M5.10
XH1: 2J1.14, 5J1.6, C9.3, D3.2, E8.13, F4.2, F8.10, L6.2
XH2: 2J1.13, 5J1.12, 5K1.13, 5L1.9, D3.15, E6.1, E8.6, F4.15, F8.3, L6.3
XH3: 2J1.12, 8H1.2, D3.11, E6.5, F4.11, L6.1
XH4: 2J1.11, 4J1.1, 8H1.5, D2.6, E8.10, F3.6, F8.13
XH5: 1J1.14, 4J1.2, 8H1.14, D2.2, E8.3, F3.2, F8.6
XH6: 1J1.13, 4J1.3, 8H1.11, B6.9, B7.5, D2.15, E7.13, F3.15, F7.10
XH7: 1J1.12, 9H1.14, E6.9, E7.3, F7.6
XH8: 1J1.11, 4J1.4, 5L1.1, 5M1.4, B6.3, E7.6, F7.3, L2.5
XH_SH: A7.3, C10.13, F7.1, F8.1
XH_SL: A7.6, C10.10, E7.1, E8.1
~BC1: 5H1.4, 7D1.1, 9E1.15
~BDIR: 5H1.5, 9E1.14
~BH1_CLK: 3B1.11, 7E1.11, 8D1.11
~BH2_CLK: 3B1.12, 8E1.11
~BUSACK: 8J1.10, 11J1.23
~BUSRQ: 8J1.7, 11J1.25
~BXH1_CLK: H9.11, J10.11, L6.5
~BXH2_CLK: H10.11, L6.4
~CHARCS: 3B1.6, 6J1.13
~CK6: 3M1.7, 5H1.13, 5K1.1, 5M1.2, 8J1.14, L7.3
~CLK6: 5L1.10, 5M1.5, 5M1.10
~CLK_LVBL: 3L1.11, 4M1.8, 6E1.9
~COL_CLK: 4H1.3, 4H1.11, 7D1.6
~CSCD: 3B1.1, 4K1.1, 5H1.2, 10K1.9
~INT: 6K1.5, 11J1.16
~IORQ: 6H1.4, 11J1.20
~IRQACK: 6H1.6, 6K1.4, 6K1.13, 6M1.1
~LMA_S: M9.1, M10.1, N11.8
~LMB_S: M3.1, M4.1, N11.6
~M1: 6H1.5, 11J1.27
~MREQ: 10K1.5, 11J1.19
~OABC_CLK: A8.2, A9.2, A10.2, C9.4, C9.9, C10.1, C11.11, F5.2, F6.2
~OTCQ1: A8.1, B6.12, D11.9
~OT_CLK: A6.6, A7.9, B7.10, D11.13
~PSG0RD: 9E1.12, 11F1.6
~PSG1RD: 9E1.13, 10H1.6
~RD: 8M1.22, 9J1.7, 11J1.21
~RFSH: 10K1.6, 11J1.28
~RQB: 8J1.6, C10.5, C11.5
~RQB_CLK: 7B1.9, C11.3
~S2F: 1L1.10, B7.9, B8.13, C7.5
~SCR2_CLK: H3.11, M1.8, N1.3
~SCRH_CLK: A5.2, B5.6, B8.9
~SLATCHCS: 9B1.12, 9F1.1
~SNCS: 8B1.2, 9B1.11, 9E1.4, 9E1.5
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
